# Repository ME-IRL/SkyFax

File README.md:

# SkyFax Modems

Fax and data modems built around Skyworks's [ISOModem chips](https://www.skyworksinc.com/en/Products/Modems-and-DAAs).

Current functional version is 4.1 (see 3.0 below):

## Case

I've also designed and printed a case to go with it. The STL files can be found under [/case](/case). Or on [OnShape](https://cad.onshape.com/documents/ec3c126b0fcf528ada2a864d/w/a2689da35195e5fe9917eb13/e/6bc9b2e75f28a1d3ae68eb94?renderMode=0&uiState=66b1e84c84b2ab750eaa0002).

Version 3.0:

## Simple Line Simulator

If you don't have access to a working landline or a proper telephone line simulator two modems can be connected back to back directly.

There are [this](https://tldp.org/HOWTO/Modem-HOWTO-26.html) and [this](https://mattfife.com/?p=4765) pages, but I have found this circuit to work for me:

The voltage and resistance can be tweaked to provide ~20mA of current with the modem/phone off-hook.

If you'd like the schematic or just have a PCB made for the line simulator, check out the [LineSim](/LineSim) project included in this repo.

Once hooked up, you want to disable the dialtone detection with the command `ATX3`. Then you can just dial with `ATDT` on one modem and answer with `ATA` on the other.

See [AN93](/docs/AN93.pdf) section 5.4 for details on all the AT commands supported.

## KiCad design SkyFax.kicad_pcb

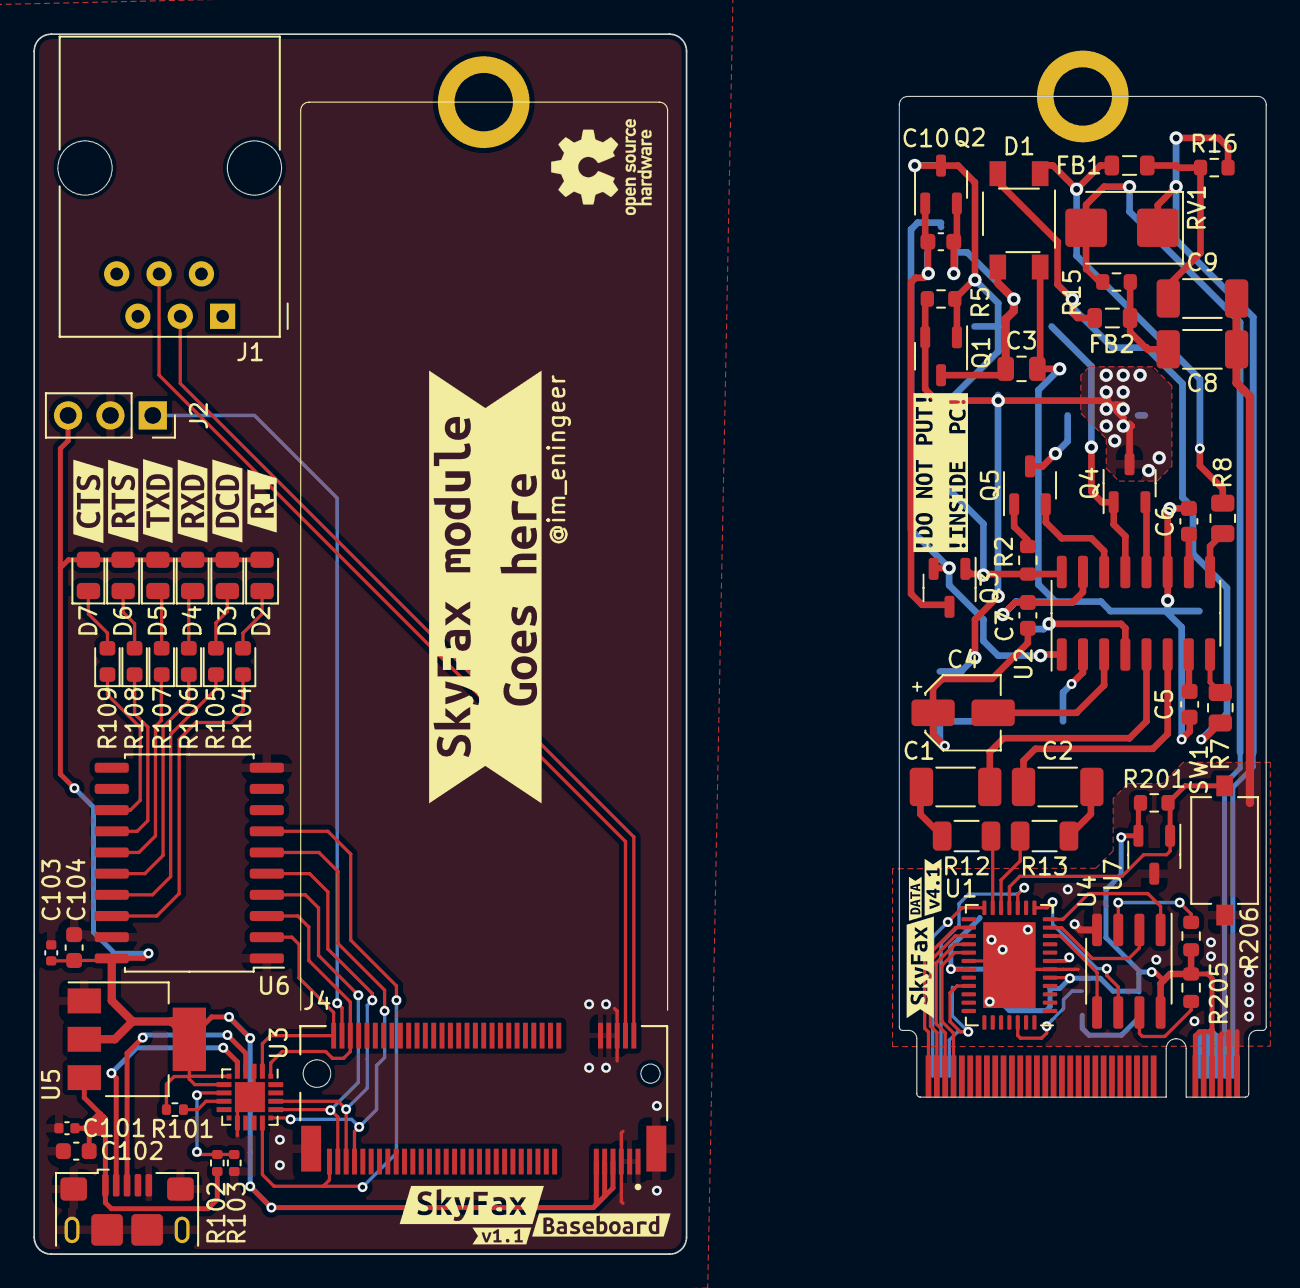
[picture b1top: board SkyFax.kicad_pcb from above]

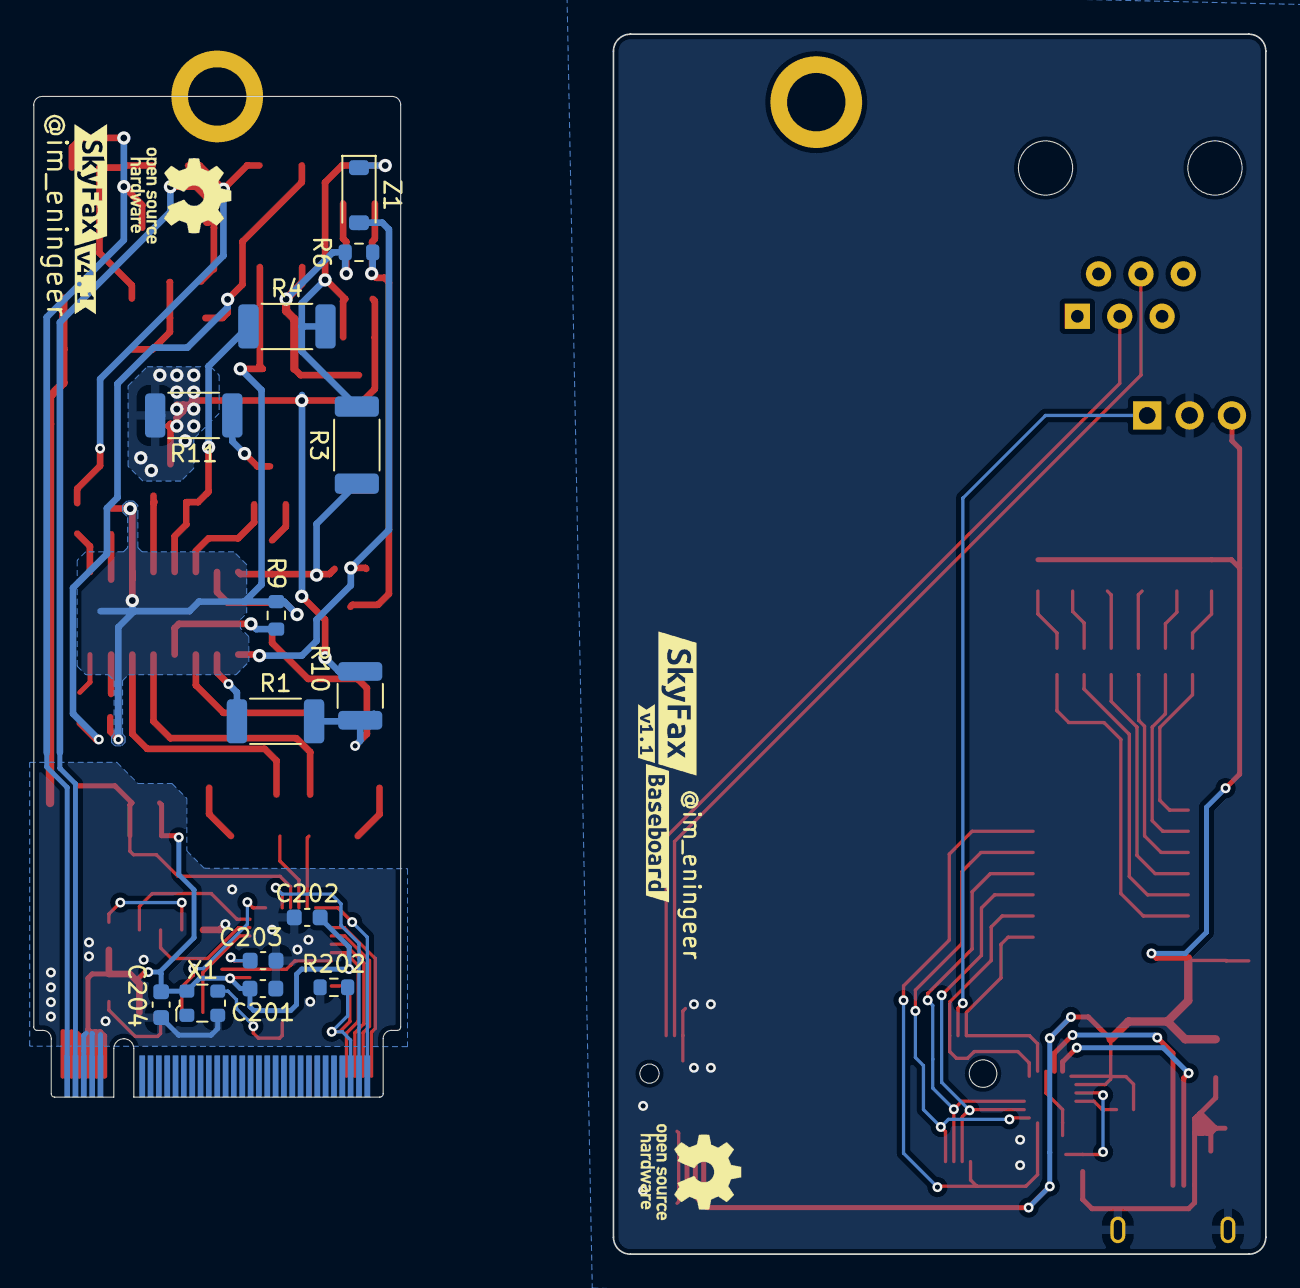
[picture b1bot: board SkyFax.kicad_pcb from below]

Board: 2 copper layers, 73.8 x 73.2 mm, 95 parts (19 on the bottom side), 76 nets.

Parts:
C1, C2: 33pF; C_1808
C3: 10nF; C_0805_2012Metric
C4: 1uF; CP_Elec_4x3
C5, C6, C102, C104, C201, C202, C204: 0.1uF; C_0603_1608Metric
C7: 2.7nF; C_0603_1608Metric
C8, C9: 680pF; C_1808
C10: 0.01uF; C_0603_1608Metric
C101, C103: 4.7uF; C_0402_1005Metric
C203: 0.22uF; C_0603_1608Metric
D1: HDS10M; Diodes_Inc_4-SMD
D2, D3, D4, D5, D6, D7: LED; LED_0805_2012Metric
FB1, FB2: FerriteBead_Small; L_0805_2012Metric
J1: RJ11/12; RJ12_Amphenol_54601
J2: Audio; PinSocket_1x03_P2.54mm_Vertical
J3: USB_B_Micro; USB_Micro-B_Amphenol_10118193-0001LF_Horizontal
J4: M.2_B_Connector; AMPHENOL_MDT420B01001_2260
J7: M.2_B_Edge; M.2-B-KEY_2260
Q1, Q3, Q4, Q5: Q_NPN_BEC; SOT-23-3
Q2: Q_PNP_BEC; SOT-23-3
R1: 1.07k; R_2010_5025Metric
R2: 150; R_0603_1608Metric
R3: 3.65k; R_2010_5025Metric
R4: 2.49k; R_2010_5025Metric
R5, R6: 100k; R_0603_1608Metric
R7, R8: 20M; R_0805_2012Metric
R9: 1M; R_0603_1608Metric
R10: 536; R_1210_3225Metric
R11: 73.2; R_2010_5025Metric
R12, R13: 56.2; R_1206_3216Metric
R15, R16: 0; R_0603_1608Metric
R101: 1k; R_0402_1005Metric
R102: 22.1k; R_0402_1005Metric
R103: 47.5k; R_0402_1005Metric
R104, R105, R106, R107, R108, R109: 220; LED_0603_1608Metric
R201, R202, R205, R206: 10k; R_0603_1608Metric
RV1: D_SMB
SW1: SW_Push; SW_Tactile_SPST_NO_Straight_CK_PTS636Sx25SMTRLFS
U1: Si2494-A-FM; QFN-38-1EP_5x7mm_P0.5mm_EP3.15x5.15mm
U2: Si3018; SOIC-16_3.9x9.9mm_P1.27mm
U3: CP2102N-Axx-xQFN20; SiliconLabs_QFN-20-1EP_3x3mm_P0.5mm_EP1.8x1.8mm
U4: 25LC640AT-E/SN; SOIC-8_3.9x4.9mm_P1.27mm
U5: AZ1117-3.3; SOT-223-3_TabPin2
U6: 74LCX541; SOIC-20W_7.5x12.8mm_P1.27mm
U7: DS1818; SOT-23-3
X1: ECS-2520MV-xxx-xx; Oscillator_SMD_ECS_2520MV-xxx-xx-4Pin_2.5x2.0mm
Z1: D_Zener; D_SOD-123
kibuzzard-650CCF10: G***; kibuzzard-650CCF10
kibuzzard-650CCF19: G***; kibuzzard-650CCF19
kibuzzard-6508DE31: G***; kibuzzard-6508DE31
kibuzzard-6508DE41: G***; kibuzzard-6508DE41
kibuzzard-650110F6: G***; kibuzzard-650110F6
kibuzzard-650111BC: G***; kibuzzard-650111BC
kibuzzard-650123DF: G***; kibuzzard-650123DF
kibuzzard-650125E8: G***; kibuzzard-650125E8
kibuzzard-6501311A: G***; kibuzzard-6501311A
kibuzzard-6501314E: G***; kibuzzard-6501314E
kibuzzard-6501315C: G***; kibuzzard-6501315C
kibuzzard-6501316E: G***; kibuzzard-6501316E
kibuzzard-6501317F: G***; kibuzzard-6501317F
kibuzzard-6501337B, kibuzzard-6501337B#2: G***; kibuzzard-6501337B
kibuzzard-65013126: G***; kibuzzard-65013126
kibuzzard-65013388, kibuzzard-65013388#2: G***; kibuzzard-65013388
kibuzzard-65013408: G***; kibuzzard-65013408

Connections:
+3V3: C103.2, C104.2, C201.2, C202.2, C204.2, D2.2 (A), D3.2 (A), D4.2 (A), D5.2 (A), D6.2 (A), D7.2 (A), J2.3, J4.7, J4.9, J4.11, J7.7, J7.9, J7.11, R101.1, R201.1, R205.1, R206.1, U1.5 (VDD), U1.26 (VDD), U3.6 (VDD), U3.7 (VREGIN), U4.8 (VCC), U5.2 (VO), U6.20 (VCC), U7.2 (VCC), X1.4 (VDD)
/MOD_AOUT: J7.72, U1.15 (AOUT)
/MOD_CTS: J7.75, U1.21 (nCTS_SCLKC_nCS)
/MOD_DCD: J7.70, R202.1, U1.28 (nDCD_D6)
/MOD_RI: J7.74, U1.19 (nRI)
/MOD_RING: J7.4, R15.2, RV1.2
/MOD_RTS: J7.69, U1.24 (nRTS_nSS_D7)
/MOD_RXD: J7.73, U1.22 (RXD_MISO_nRD)
/MOD_TIP: J7.2, R16.2, RV1.1
/MOD_TXD: J7.71, U1.23 (TXD_MOSI_nWR)
/SI2494/C1A: R12.1, U1.18 (C1A)
/SI2494/C2A: R13.1, U1.17 (C2A)
/SI2494/EECLK: U1.13 (EECLK), U4.6 (SCK)
/SI2494/EECS: U1.12 (nEECS), U4.1 (~CS)
/SI2494/EESDI: U1.10 (EESDI), U4.5 (MOSI)
/SI2494/EESDO: U1.11 (EESDO), U4.2 (MISO)
/SI2494/RST: R201.2, SW1.2, U1.16 (nRST), U7.1 (RST)
/SI3018/C1A: C1.1, U2.5 (C1B)
/SI3018/C2A: C2.1, U2.6 (C2B)
/USB_AOUT: J2.1, J4.72
/USB_CTS: J4.75, U3.15 (~CTS), U6.7 (A5)
/USB_DCD: J4.70, U3.1 (RS485/GPIO.1), U6.3 (A1)
/USB_RI: J4.74, U3.2 (CLK/GPIO.0), U6.2 (A0)
/USB_RING: J1.4, J4.4
/USB_RTS: J4.69, U3.16 (~RTS), U6.6 (A4)
/USB_RXD: J4.73, U3.17 (RXD), U6.4 (A2)
/USB_TIP: J1.3, J4.2
/USB_TXD: J4.71, U3.18 (TXD), U6.5 (A3)
GND: C8.2, C9.2, C101.1, C102.1, C103.1, C104.1, C201.1, C202.1, C203.1, C204.1, J2.2, J3.5 (GND), J3.6 (Shield), J4.1, J4.3, J4.5, J4.6, J4.8, J4.10, J4.S1 (SHIELD), J4.S2 (SHIELD), J7.1, J7.3, J7.5, J7.6, J7.8, J7.10, R103.2, R202.2, SW1.1, U1.6 (GND), U1.25 (GND), U1.39 (EP), U3.3 (GND), U3.12 (GND), U3.21 (GND), U4.4 (GND), U5.1 (GND), U6.1 (G1), U6.10 (GND), U6.19 (G2), U7.3 (GND), X1.2 (GND)
GND1: C3.2, C5.2, C6.2, C7.1, D1.3 (-), R9.1, U2.11 (SC), U2.15 (IGND)
unnamed: C1.2, R12.2
unnamed: C2.2, R13.2
unnamed: C4.1, C7.2, R1.2, R10.1
unnamed: C8.1, FB2.2, R15.1
unnamed: C9.1, FB1.2, R16.1
unnamed: C3.1, C10.1, D1.1 (+), Q1.3 (C), Q2.2 (E), R6.1
unnamed: D1.2, FB2.1, R7.1
unnamed: D1.4, FB1.1, R8.2
unnamed: D2.1 (K), R104.2
unnamed: D3.1 (K), R105.2
unnamed: D4.1 (K), R106.2
unnamed: D5.1 (K), R107.2
unnamed: D6.1 (K), R108.2
unnamed: D7.1 (K), R109.2
unnamed: J3.3 (D+), U3.4 (D+)
unnamed: J3.2 (D-), U3.5 (D-)
unnamed: Q1.1 (B), Q2.3 (C), R3.2, R4.2, R5.1, Z1.1 (K)
unnamed: Q1.2 (E), Q4.3 (C), R5.2, R10.2, R11.2
unnamed: C10.2, Q2.1 (B), Q3.3 (C), R6.2
unnamed: Q3.1 (B), R2.1, R3.1, U2.16 (DCT2)
unnamed: Q3.2 (E), U2.1 (QE), Z1.2 (A)
unnamed: Q4.1 (B), R4.1, U2.13 (QB)
unnamed: Q4.2 (E), U2.12 (QE2)
unnamed: Q5.1 (B), R2.2
unnamed: Q5.3 (C), R11.1
unnamed: Q5.2 (E), U2.14 (DCT3)
unnamed: U1.36 (CLKIN_XTAL1), X1.3 (OUT)
unnamed: C203.2, U1.7 (VREG)
unnamed: R1.1, U2.2 (DCT)
unnamed: R9.2, U2.4 (IB)
unnamed: R7.2, U2.8 (RNG1)
unnamed: R8.1, U2.9 (RNG2)
unnamed: C4.2, U2.3 (RX)
unnamed: C6.1, U2.10 (VREG2)
unnamed: C5.1, U2.7 (VREG)
unnamed: R102.2, R103.1, U3.8 (VBUS)
unnamed: R101.2, U3.9 (~RST)
unnamed: R205.2, U4.7 (~HOLD)
unnamed: R206.2, U4.3 (~WP)
unnamed: R104.1, U6.18 (Y0)
unnamed: R105.1, U6.17 (Y1)
unnamed: R106.1, U6.16 (Y2)
unnamed: R107.1, U6.15 (Y3)
unnamed: R108.1, U6.14 (Y4)
unnamed: R109.1, U6.13 (Y5)
VBUS: C101.2, C102.2, J3.1 (VBUS), R102.1, U5.3 (VI)

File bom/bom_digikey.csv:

"Reference","Value","Footprint","DIGIKEY","Qty"
"C1, C2","33pF","FaxCam:C_1808","732-8853520100071CT-ND","2"
"C3","10nF","Capacitor_SMD:C_0805_2012Metric","2679-C0805X7R251-103KNE-CT-ND","1"
"C4","1uF","Capacitor_SMD:CP_Elec_4x3","PCE3912CT-ND","1"
"C5, C6, C102, C104, C201, C202, C204","0.1uF","Capacitor_SMD:C_0603_1608Metric","2679-C0603X7R160-104MNE-CT-ND","7"
"C7","2.7nF","Capacitor_SMD:C_0603_1608Metric","2679-C0603X7R500-272MNE-CT-ND","1"
"C8, C9","680pF","FaxCam:C_1808","4587-SCC1808X681K502TGCT-ND","2"
"C10","0.01uF","Capacitor_SMD:C_0603_1608Metric","2679-C0603X7R160-103MNE-CT-ND","1"
"C101, C103","4.7uF","Capacitor_SMD:C_0402_1005Metric","1276-1482-1-ND","2"
"C203","0.22uF","Capacitor_SMD:C_0603_1608Metric","1292-1420-1-ND","1"
"D1","HDS10M","FaxCam:Diodes_Inc_4-SMD","HDS10M-13DICT-ND","1"
"D2-D7","LED","LED_SMD:LED_0805_2012Metric","160-1427-1-ND","6"
"FB1, FB2","FerriteBead_Small","Inductor_SMD:L_0805_2012Metric","490-1040-1-ND","2"
"J1","RJ11/12","Connector_RJ:RJ12_Amphenol_54601","609-5080-ND","1"
"J2","Audio","Connector_PinSocket_2.54mm:PinSocket_1x02_P2.54mm_Vertical","","1"
"J3","USB_B_Micro","Connector_USB:USB_Micro-B_Amphenol_10118193-0001LF_Horizontal","609-4616-1-ND","1"
"J4","M.2_B_Connector","SkyFax:AMPHENOL_MDT420B01001_2260","MDT420B01001CT-ND","1"
"J7","M.2_B_Edge","SkyFax:M.2-B-KEY_2260","","1"
"Q1, Q3","Q_NPN_BEC","Package_TO_SOT_SMD:SOT-23-3","MMBTA42LT1GOSCT-ND","2"
"Q2","Q_PNP_BEC","Package_TO_SOT_SMD:SOT-23-3","MMBTA92LT1GOSCT-ND","1"
"Q4, Q5","Q_NPN_BEC","Package_TO_SOT_SMD:SOT-23-3","MMBTA06LT1GOSCT-ND","2"
"R1","1.07k","Resistor_SMD:R_2010_5025Metric","13-RC2010FK-071K07LCT-ND","1"
"R2","150","Resistor_SMD:R_0603_1608Metric","311-150HRCT-ND","1"
"R3","3.65k","Resistor_SMD:R_2010_5025Metric","13-RC2010FK-073K65LCT-ND","1"
"R4","2.49k","Resistor_SMD:R_2010_5025Metric","738-RMCF2010FT2K49CT-ND","1"
"R5, R6","100k","Resistor_SMD:R_0603_1608Metric","A130103CT-ND","2"
"R7, R8","20M","Resistor_SMD:R_0805_2012Metric","13-RC0805JR-0720MLCT-ND","2"
"R9","1M","Resistor_SMD:R_0603_1608Metric","A121559CT-ND","1"
"R10","536","Resistor_SMD:R_1210_3225Metric","541-536AACT-ND","1"
"R11","73.2","Resistor_SMD:R_2010_5025Metric","13-RC2010FK-0773R2LCT-ND","1"
"R12, R13","56.2","Resistor_SMD:R_1206_3216Metric","RNCP1206FTD56R2CT-ND","2"
"R15, R16","0","Resistor_SMD:R_0603_1608Metric","36-5110CT-ND","2"
"R101","1k","Resistor_SMD:R_0402_1005Metric","311-1.0KJRCT-ND","1"
"R102","22.1k","Resistor_SMD:R_0402_1005Metric","311-22.1KLRCT-ND","1"
"R103","47.5k","Resistor_SMD:R_0402_1005Metric","311-47.5KLRCT-ND","1"
"R104-R109","220","LED_SMD:LED_0603_1608Metric","A130087CT-ND","6"
"R201, R202, R205, R206","10k","Resistor_SMD:R_0603_1608Metric","RNCP0603FTD10K0CT-ND","4"
"RV1","~","Diode_SMD:D_SMB","P3100SBLRPCT-ND","1"
"SW1","SW_Push","Button_Switch_SMD:SW_Tactile_SPST_NO_Straight_CK_PTS636Sx25SMTRLFS","CKN12322-1-ND","1"
"U1","Si2494-A-FM","Package_DFN_QFN:QFN-38-1EP_5x7mm_P0.5mm_EP3.15x5.15mm","SI2494-A-FM-ND","1"
"U2","Si3018","Package_SO:SOIC-16_3.9x9.9mm_P1.27mm","336-4140-2-ND","1"
"U3","CP2102N-Axx-xQFN20","Package_DFN_QFN:SiliconLabs_QFN-20-1EP_3x3mm_P0.5mm_EP1.8x1.8mm","336-5886-1-ND","1"
"U4","25LC640AT-E/SN","Package_SO:SOIC-8_3.9x4.9mm_P1.27mm","25LC640AT-E/SNCT-ND","1"
"U5","AZ1117-3.3","Package_TO_SOT_SMD:SOT-223-3_TabPin2","AZ1117IH-3.3TRG1DICT-ND","1"
"U6","74LCX541","Package_SO:SOIC-20W_7.5x12.8mm_P1.27mm","74LCX541WMXCT-ND","1"
"U7","DS1818","Package_TO_SOT_SMD:SOT-23-3","DS1818R-10+CT-ND","1"
"X1","ECS-2520MV-xxx-xx","Oscillator:Oscillator_SMD_ECS_2520MV-xxx-xx-4Pin_2.5x2.0mm","XC3186CT-ND","1"
"Z1","D_Zener","Diode_SMD:D_SOD-123","BZT52C43-FDICT-ND","1"

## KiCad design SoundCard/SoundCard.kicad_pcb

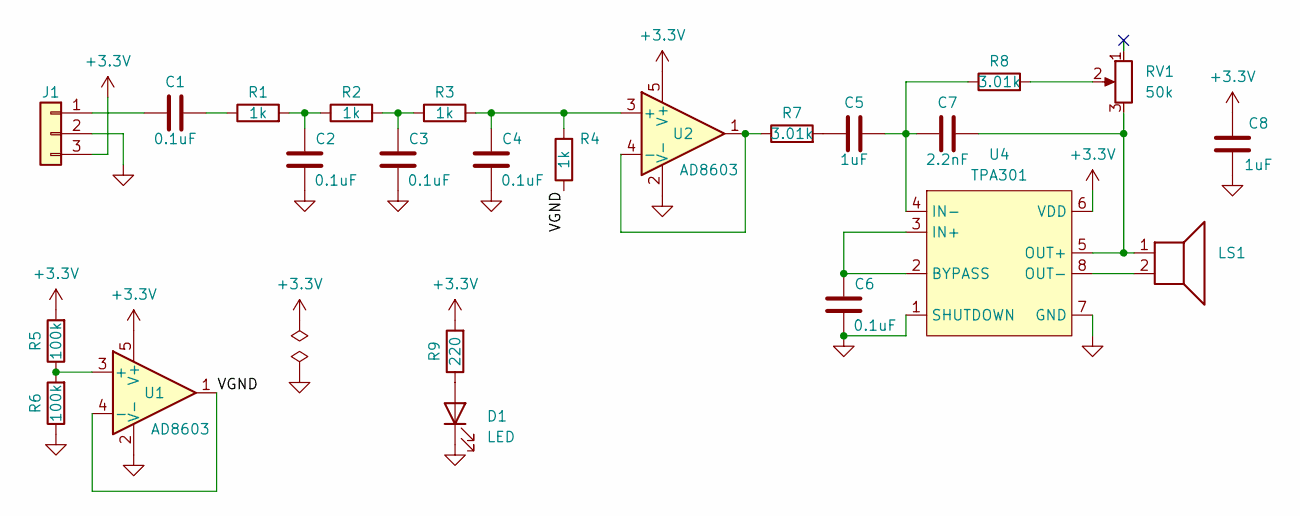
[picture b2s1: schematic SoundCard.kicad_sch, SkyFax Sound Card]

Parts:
C1, C2, C3, C4, C6: 0.1uF; C_0402_1005Metric; DIGIKEY 1276-1043-1-ND
C5, C8: 1uF; C_0402_1005Metric; DIGIKEY 1276-1076-1-ND
C7: 2.2nF; C_0402_1005Metric; DIGIKEY 490-GCM155R71H222KA37JCT-ND
D1: LED; LED_0805_2012Metric; DIGIKEY 160-1427-1-ND
J1: Conn_01x03; PinHeader_1x03_P2.54mm_Vertical
LS1: Speaker; PC_Speaker_15.0mm; DIGIKEY 102-2498-ND
R1, R2, R3, R4: 1k; R_0402_1005Metric; DIGIKEY MCS0402-1.00K-CFCT-ND
R5, R6: 100k; R_0402_1005Metric; DIGIKEY YAG2304CT-ND
R7, R8: 3.01k; R_0402_1005Metric; DIGIKEY 311-3.01KLRCT-ND
R9: 220; R_0402_1005Metric; DIGIKEY A130087CT-ND
RV1: 50k; Potentiometer_Bourns_TC33X_Vertical; DIGIKEY 118-TC33X-2-503GCT-ND
U1, U2: AD8603; TSOT-23-5; DIGIKEY AD8603AUJZ-REELCT-ND
U4: TPA301; SOIC-8_3.9x4.9mm_P1.27mm; DIGIKEY 296-1945-1-ND

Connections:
+3.3V: C8.2, J1.3, R5.2, R9.2, U1.5 (V+), U2.5 (V+), U4.6 (VDD)
/VGND: R4.1, U1.1, U1.4 (-)
GND: C2.2, C3.2, C4.2, C6.2, C8.1, D1.1 (K), J1.2, R6.1, U1.2 (V-), U2.2 (V-), U4.1 (SHUTDOWN), U4.7 (GND)
unnamed: C1.2, R1.1
unnamed: C2.1, R1.2, R2.1
unnamed: C3.1, R2.2, R3.1
unnamed: C5.1, R7.2
unnamed: D1.2 (A), R9.1
unnamed: C1.1, J1.1
unnamed: R8.2, RV1.2
unnamed: R5.1, R6.2, U1.3 (+)
unnamed: C4.1, R3.2, R4.2, U2.3 (+)
unnamed: R7.1, U2.1, U2.4 (-)
unnamed: C6.1, U4.2 (BYPASS), U4.3 (IN+)
unnamed: C5.2, C7.1, R8.1, U4.4 (IN-)
unnamed: C7.2, LS1.1, RV1.3, U4.5 (OUT+)
unnamed: LS1.2, U4.8 (OUT-)

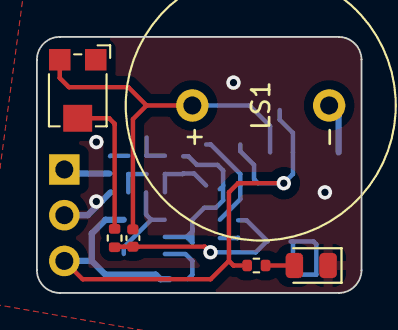
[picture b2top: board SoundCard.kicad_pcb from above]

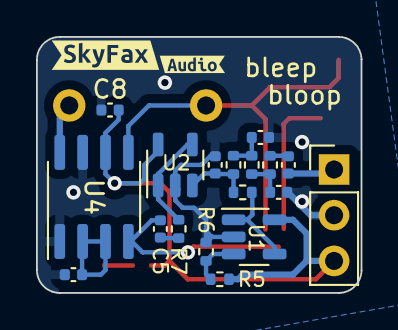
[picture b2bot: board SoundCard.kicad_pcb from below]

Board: 2 copper layers, 18.0 x 14.2 mm, 26 parts (20 on the bottom side), 17 nets.

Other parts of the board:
kibuzzard-650CC8A2: G***; kibuzzard-650CC8A2
kibuzzard-650CC8CA: G***; kibuzzard-650CC8CA

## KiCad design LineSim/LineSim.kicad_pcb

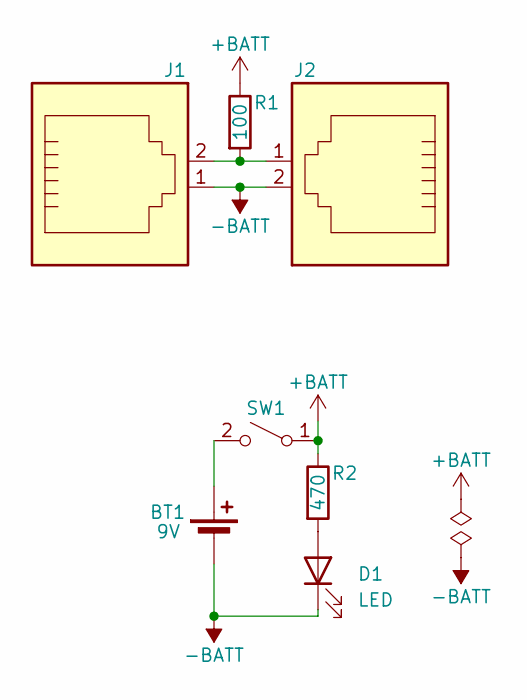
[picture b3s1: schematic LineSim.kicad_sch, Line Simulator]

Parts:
BT1: 9V; BAT_BH9VPC; DIGIKEY BH9V-PC-ND
D1: LED; LED_D5.0mm; DIGIKEY 754-1264-ND
J1, J2: RJ11; DIGIKEY 609-5080-ND
R1: 100; R_Axial_DIN0207_L6.3mm_D2.5mm_P7.62mm_Horizontal; DIGIKEY CF14JT100RCT-ND
R2: 470; R_Axial_DIN0207_L6.3mm_D2.5mm_P7.62mm_Horizontal; DIGIKEY CF14JT470RCT-ND
SW1: SW_SPST; SW_GF-123-0054; DIGIKEY CWI333-ND

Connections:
+BATT: R1.1, R2.1, SW1.1 (A)
-BATT: BT1.2 (-), D1.1 (K), J1.1, J2.2
unnamed: BT1.1 (+), SW1.2 (B)
unnamed: D1.2 (A), R2.2
unnamed: J1.2, J2.1, R1.2

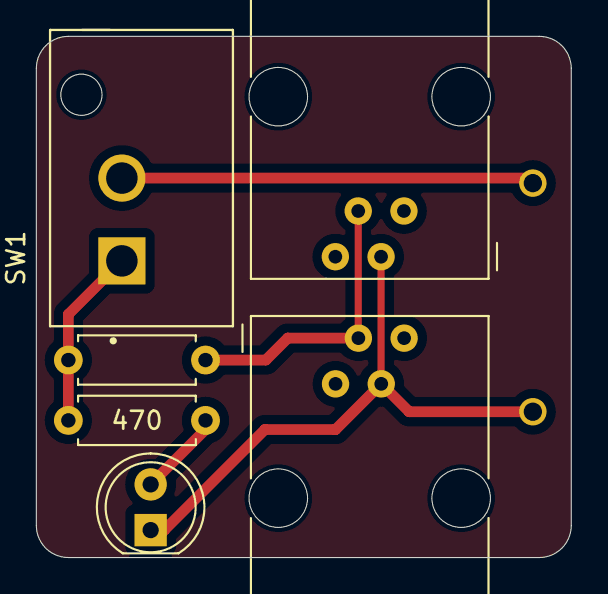
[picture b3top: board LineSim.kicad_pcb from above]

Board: 4 copper layers, 29.7 x 29.0 mm, 7 parts (1 on the bottom side), 5 nets.

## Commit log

2023-07-04 Initial.
    Schematics v1.0
    Working on PCB layout
2023-07-04 Sent to fab v1.0
2023-07-16 Version 2.0 Schematics
2023-07-17 Layout v1.9 (not finished)
2023-08-18 Sent to fab v2.0
2023-09-03 Schematics v3.0
2023-09-03 Sent to fab v3.0
2023-09-11 Version 3.0 minor BOM changes
2023-09-11 Version 3.0 ERC/DRC fixes
2023-09-11 [3.0*] Fix 3D models
2023-09-11 [3.0] BOM + Gerbers
2023-09-13 [4.0] M.2 Module. Sent to fab
2023-09-13 [docs] Add README + datasheets
2023-09-18 [4.1] Fix minor layout + BoM issue
    X1, C204, R202 were too close to M.2 connector edge
    Didn't realize one of the components were not included in the BoM (Q1,Q3)
2023-09-18 [docs] README update
2023-09-21 [docs] Add line simulator circuit
2023-09-21 [docs] Fix line_sim circuit
2023-09-21 [line-sim] Line simulator KiCad
2023-09-21 [4.2] Sound card
2024-08-06 Add case and photos
